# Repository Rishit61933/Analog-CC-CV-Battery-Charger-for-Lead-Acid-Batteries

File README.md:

# Analog-CC-CV-Battery-Charger-for-Lead-Acid-Batteries

> A fully analog, microcontroller-free smart battery charger for 12V lead-acid batteries — automatically manages Constant Current, Constant Voltage, and Trickle Charge phases using only op-amps, transistors, and MOSFETs.

**Course:** EE322 — Analog and Mixed Signal Circuits  
**Team Name:** The Semicons  
**Institute:** Indian Institute of Technology Gandhinagar

---

## 📌 Project Overview

This project implements a **low-dropout CC-CV charger** with automatic trickle charge mode — entirely in analog. No microcontrollers, no firmware, no bugs. A **P-channel MOSFET (IRF9540)** acts as the main power-pass element, with analog feedback loops handling all stage transitions automatically.

### Charging Stages

```
[Discharged Battery]
        │
        ▼
┌─────────────────┐
│  Constant       │  ← Bulk charge: fixed current, voltage rising
│  Current (CC)   │
└────────┬────────┘
         │ Vbatt reaches 14.4V
         ▼
┌─────────────────┐
│  Constant       │  ← Voltage held at 14.4V, current tapers
│  Voltage (CV)   │
└────────┬────────┘
         │ Current drops to maintenance level
         ▼
┌─────────────────┐
│  Trickle        │  ← Tiny maintenance current, prevents self-discharge
│  Charge         │
└─────────────────┘
        │
        ▼
 [Fully Charged Battery ]
```

---

## 🔧 System Architecture  

The circuit is divided into **7 functional blocks**:

| S. No. | Block Name                          |
|--------|-----------------------------------|
| 1      | AC to DC Converter                |
| 2      | Voltage Reference & Regulation    |
| 3      | Constant Current Block            |
| 4      | Switching & Output Stage          |
| 5      | Battery Simulation & Sensing      |
| 6      | Charge Indicator Block            |
| 7      | Trickle Charge Indicator Block    |
### Block Descriptions

**Block 1 — AC to DC Converter**  
Converts AC mains input to a stable ~15V DC rail using a GBU406 bridge rectifier and a 2200µF filter capacitor.

**Block 2 — Voltage Reference & Regulation**  
Uses a TL431A programmable shunt reference + 2N3904 transistor to monitor battery voltage and prevent overcharging above 14.4V.

**Block 3 — Constant Current Block**  
Limits bulk charging current to a safe preset level using TL431A, 2N3906, and 2N3904 transistors with current-sense feedback.

**Block 4 — Switching & Output Stage**  
The IRF9540 P-channel MOSFET acts as an electronic valve, throttled by control signals from the CC and CV feedback loops.

**Block 5 — Battery Simulation & Sensing**  
A 1Ω high-power shunt resistor (Rlim) senses charging current and feeds back into the CC control block.

**Blocks 6 & 7 — Charge & Trickle Indicators**  
2N7000 N-channel MOSFETs drive LEDs to visually indicate the current charging phase (CC/CV vs. Trickle).

---

## 🔩 Key Components

| Component | Role |
|---|---|
| GBU406 Bridge Rectifier | AC → DC conversion |
| 2200µF Filter Capacitor | Smoothing DC rail |
| TL431A (×2) | Programmable voltage reference (CV + CC control) |
| IRF9540 P-channel MOSFET | Main power-pass element |
| 2N3904 / 2N3906 Transistors | Control logic & feedback |
| 2N7000 N-channel MOSFETs | LED indicator drivers |
| 1Ω High-Power Resistor (Rlim) | Current sensing shunt |
| Indicator LEDs | Charge phase visual feedback |

---

## 🔌 How the Control Loop Works

The CC and CV loops **compete** to control the gate of the main MOSFET:

- **CC loop** (via matched transistor pair in U2): detects excess current → pulls MOSFET gate to throttle power
- **CV loop** (via TL431A + Q1): detects voltage exceeding 14.4V → pulls MOSFET gate to throttle power
- **Whichever limit is hit first takes control** — this is the core of the analog CC-CV switching mechanism

```
         ┌─────────────┐
         │ CC Feedback │──────┐
         │  (U2, Q3)   │      │
         └─────────────┘      ▼
                         [Q3 Base] → [Gate of IRF9540 M1] → Output to Battery
         ┌─────────────┐      ▲
         │ CV Feedback │──────┘
         │ (TL431, Q1) │
         └─────────────┘
```

---

## 🧪 Integration & Testing Plan

1. **AC-DC Block** — Verify stable ~15V DC output
2. **Voltage Reference + CC Block** — Breadboard test with lab supply to dial in setpoints
3. **Switching Stage** — Verify MOSFET gate operation in isolation
4. **CC/CV Integration** — Test with high-power dummy load; confirm stable regulation in both modes
5. **LED Indicators** — Simulate each charging phase; verify correct LEDs light up
6. **Full Battery Test** — Connect to a partially discharged 12V lead-acid battery; verify automatic CC → CV → Trickle transitions

---

## ✅ Advantages Over Alternatives

| Feature | This Design | Simple Trickle Charger | MCU-Based Charger |
|---|---|---|---|
| No firmware bugs | ✅ | ✅ | ❌ |
| Auto CC/CV/Trickle | ✅ | ❌ | ✅ |
| Overcharge protection | ✅ | ❌ | ✅ |
| Low dropout design | ✅ | ❌ | Varies |
| Fast charging | ✅ | ❌ | ✅ |
| Low complexity | ✅ | ✅ | ❌ |
| Temp stable (matched pairs) | ✅ | ❌ | ❌ |

---

## 🔮 Future Work

- Temperature-compensated charging curves for better battery longevity
- Adjustable reference to support 6V / 24V lead-acid batteries
- Add analog current/voltage meter readout
- Solar panel input integration (original planned scope)

---

## 📚 References

1. [A Low Dropout CC-CV 12V Lead Acid Battery Charger — EE World Online](https://www.eeworldonline.com/a-low-dropout-cc-cv-12v-lead-acid-battery-charger-with-auto-trickle-charge/)
2. [Lead Acid Battery Charger Reference Design — Texas Instruments SLVA576A](https://www.ti.com/lit/an/slva576a/slva576a.pdf)

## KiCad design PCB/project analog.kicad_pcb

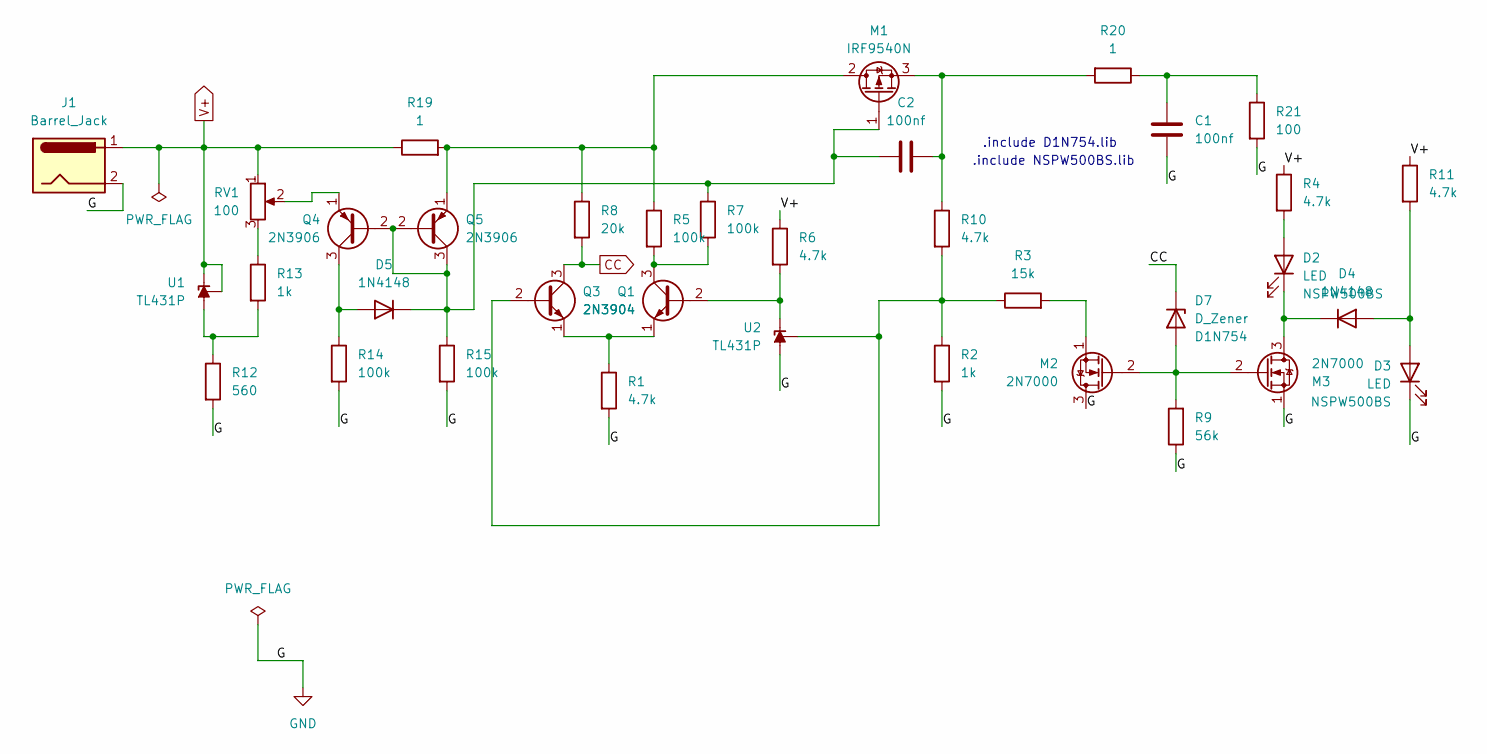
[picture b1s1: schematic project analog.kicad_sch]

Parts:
C1, C2: 100nf; CP_Radial_D12.5mm_P7.50mm
D2, D3: LED; LED_D5.0mm
D4, D5: 1N4148; D_DO-35_SOD27_P7.62mm_Horizontal
D7: D_Zener; D_DO-35_SOD27_P7.62mm_Horizontal
J1: Barrel_Jack; BarrelJack_Horizontal
M1: IRF9540N; TO-220-3_Vertical
M2, M3: 2N7000; TO-92_Inline
Q1, Q3: 2N3904; TO-92_Inline
Q4, Q5: 2N3906; TO-92_Inline
R1, R4, R6, R10, R11: 4.7k; R_Axial_DIN0309_L9.0mm_D3.2mm_P12.70mm_Horizontal
R2, R13: 1k; R_Axial_DIN0309_L9.0mm_D3.2mm_P12.70mm_Horizontal
R3: 15k; R_Axial_DIN0309_L9.0mm_D3.2mm_P12.70mm_Horizontal
R5, R7, R14, R15: 100k; R_Axial_DIN0309_L9.0mm_D3.2mm_P12.70mm_Horizontal
R8: 20k; R_Axial_DIN0309_L9.0mm_D3.2mm_P12.70mm_Horizontal
R9: 56k; R_Axial_DIN0309_L9.0mm_D3.2mm_P12.70mm_Horizontal
R12: 560; R_Axial_DIN0309_L9.0mm_D3.2mm_P12.70mm_Horizontal
R19, R20: 1; R_Axial_DIN0309_L9.0mm_D3.2mm_P12.70mm_Horizontal
R21: 100; R_Axial_DIN0309_L9.0mm_D3.2mm_P12.70mm_Horizontal
RV1: 100; Potentiometer_Bourns_3296W_Vertical
U1, U2: TL431P; DIP-8_W7.62mm

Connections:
CC: D7.1 (K), Q3.3 (C), R8.2
GND: C1.2, D3.1 (K), J1.2, M2.3 (D), M3.1 (S), R1.2, R2.2, R9.1, R12.2, R14.2, R15.2, R21.2, U2.6 (A)
unnamed: C1.1, R20.1, R21.1
unnamed: D2.2 (A), R4.2
unnamed: D2.1 (K), D4.1 (K), M3.3 (D)
unnamed: D3.2 (A), D4.2 (A), R11.2
unnamed: D5.2 (A), Q4.3 (C), R14.1
unnamed: C2.2, D5.1 (K), M1.1 (G), Q4.2 (B), Q5.2 (B), Q5.3 (C), R7.1, R15.1
unnamed: D7.2 (A), M2.2 (G), M3.2 (G), R9.2
unnamed: M1.2 (D), Q5.1 (E), R5.1, R8.1, R19.2
unnamed: C2.1, M1.3 (S), R10.1, R20.2
unnamed: M2.1 (S), R3.2
unnamed: Q1.2 (B), R6.2, U2.1 (K)
unnamed: Q1.3 (C), R5.2, R7.2
unnamed: Q1.1 (E), Q3.1 (E), R1.1
unnamed: Q3.2 (B), R2.1, R3.1, R10.2, U2.8 (REF)
unnamed: Q4.1 (E), RV1.2
unnamed: R13.1, RV1.3
unnamed: R12.1, R13.2, U1.6 (A)
V+: J1.1, R4.1, R6.1, R11.1, R19.1, RV1.1, U1.1 (K), U1.8 (REF)

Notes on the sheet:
.include D1N754.lib
.include NSPW500BS.lib

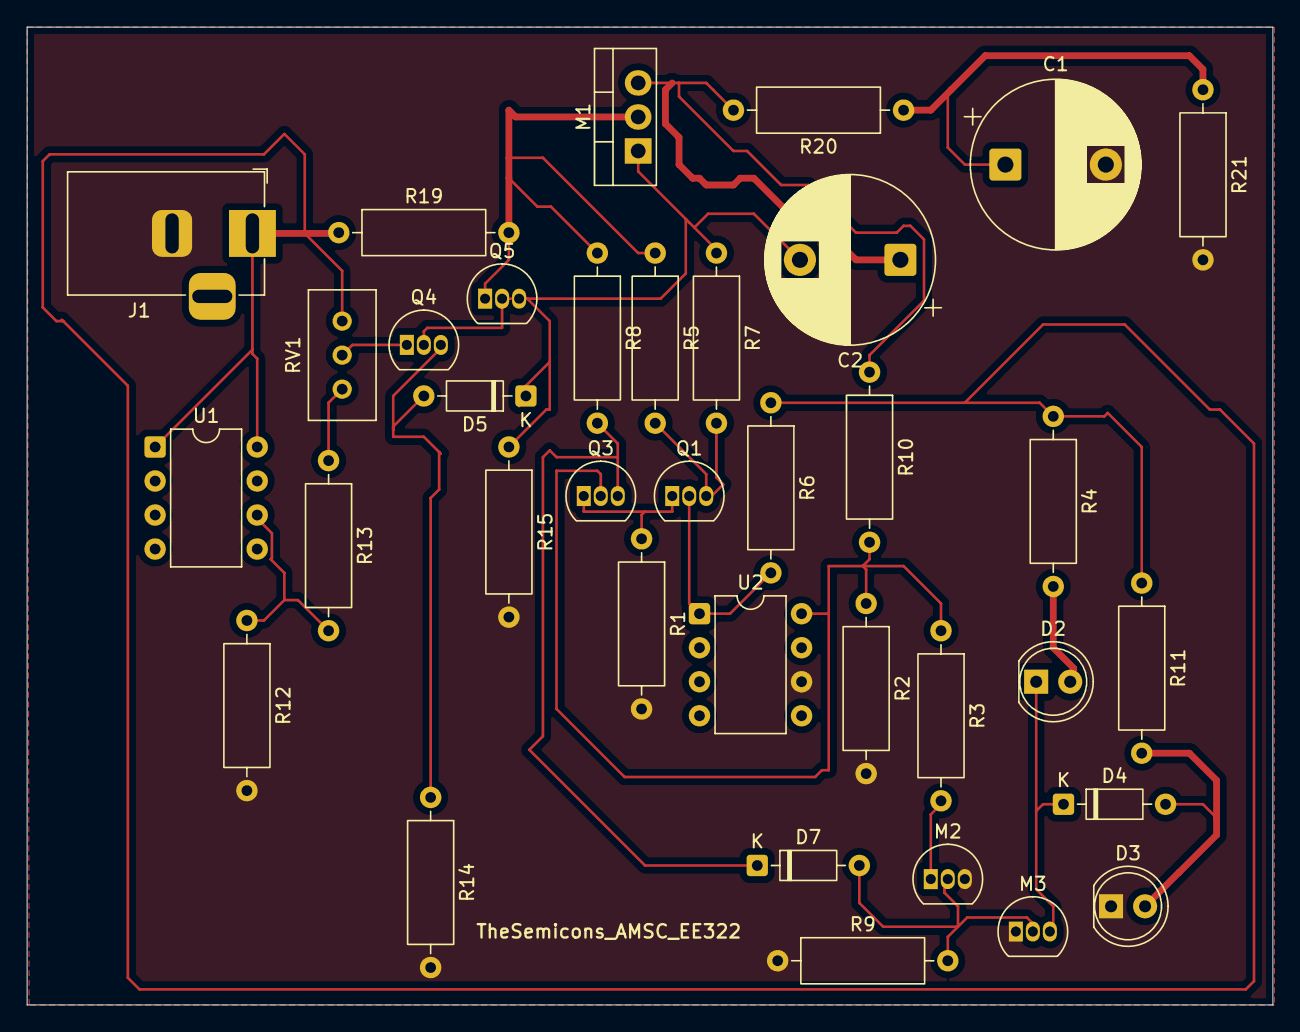
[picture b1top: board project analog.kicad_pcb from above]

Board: 2 copper layers, 93.0 x 73.0 mm, 36 parts (0 on the bottom side), 20 nets.

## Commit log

2026-04-06 README.md
2026-04-06 Rename The Semicons Project Proposal AMSC .pdf to Proposal/The Semicons Project Proposal AMSC .pdf
2026-04-06 Rename project analog.kicad_sch to Schematic/project analog.kicad_sch
2026-04-06 Rename project analog.kicad_pcb to PCB/project analog.kicad_pcb
2026-04-06 Rename project analog.kicad_pro to PCB/project analog.kicad_pro
